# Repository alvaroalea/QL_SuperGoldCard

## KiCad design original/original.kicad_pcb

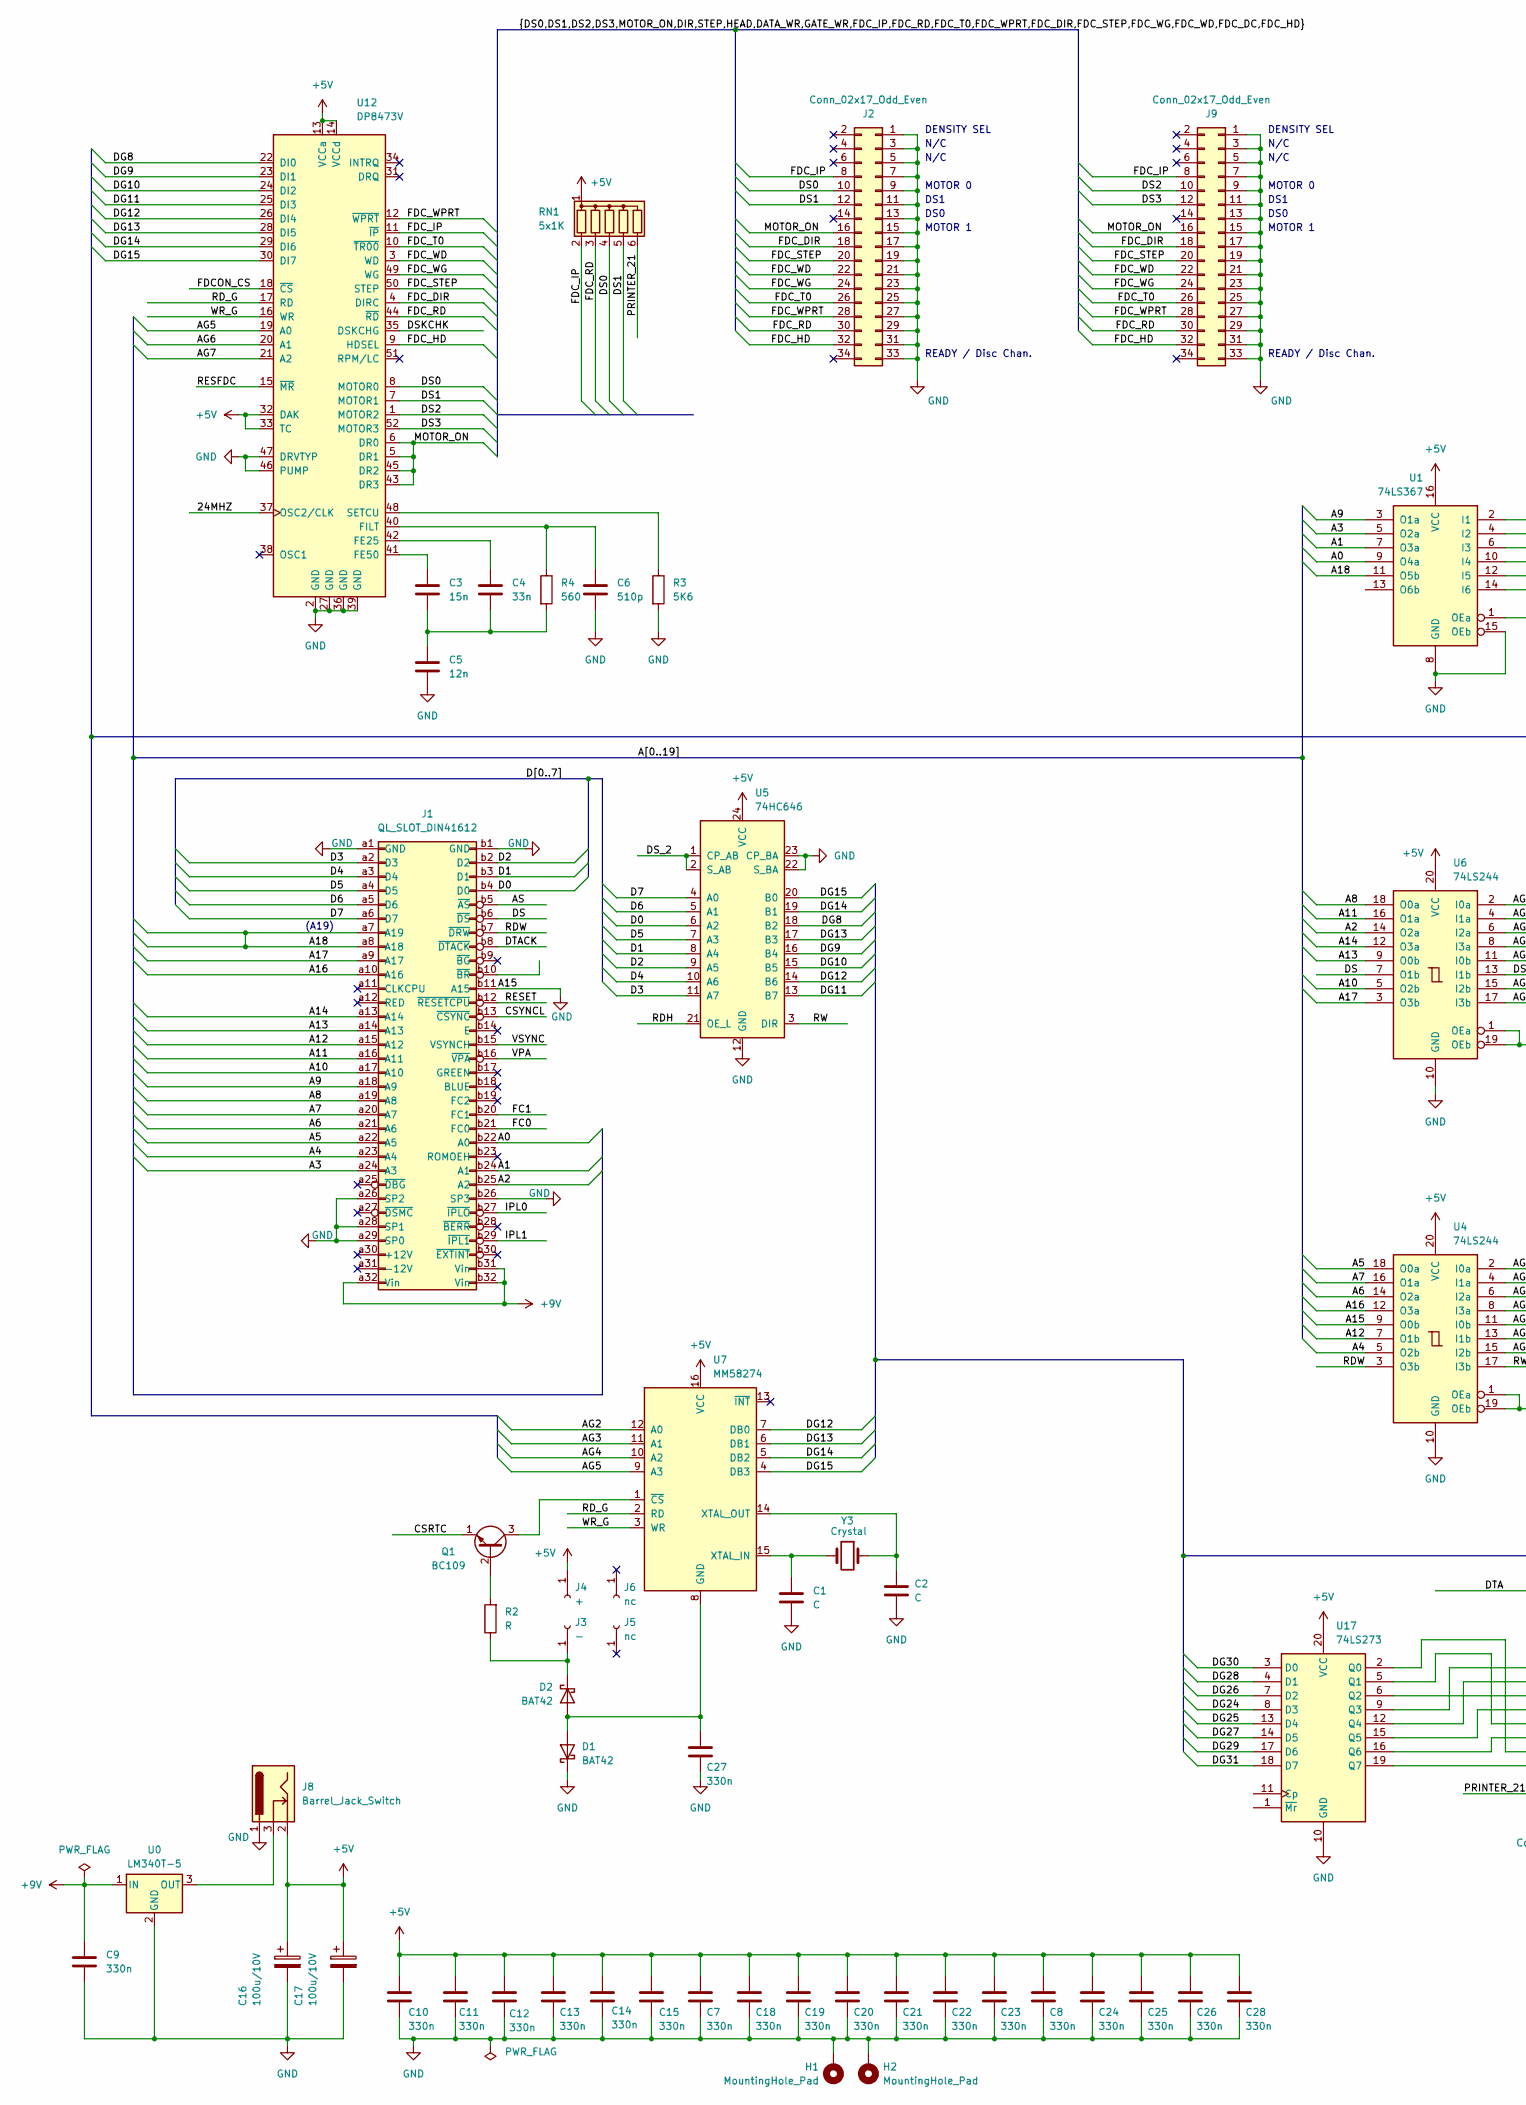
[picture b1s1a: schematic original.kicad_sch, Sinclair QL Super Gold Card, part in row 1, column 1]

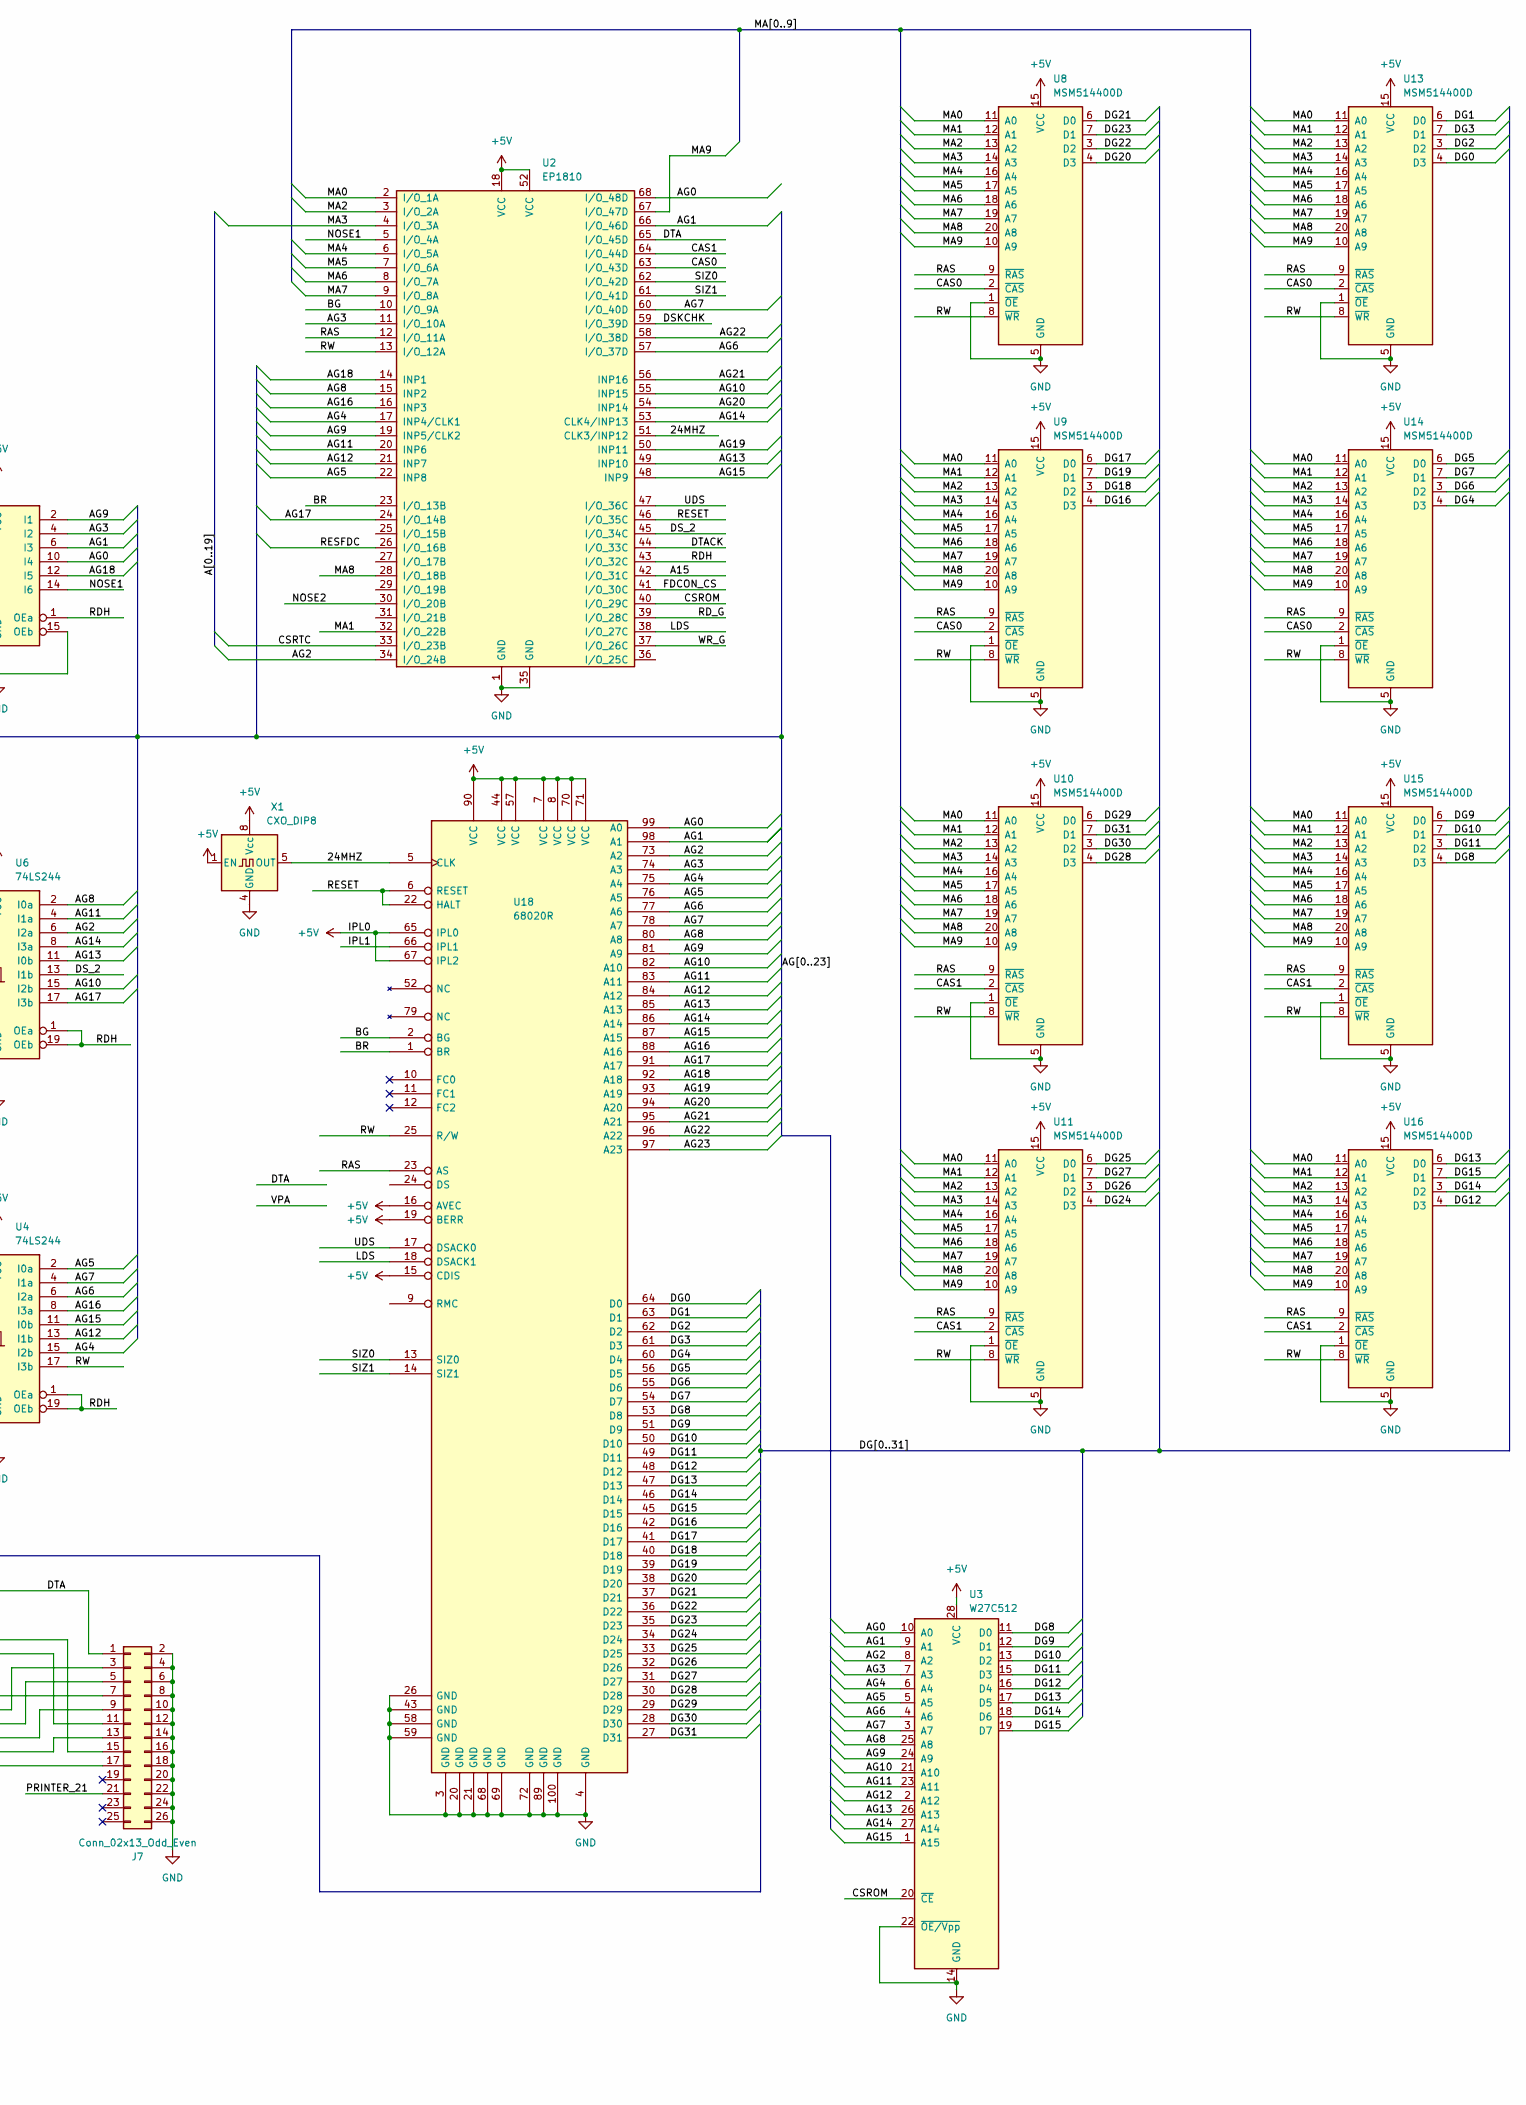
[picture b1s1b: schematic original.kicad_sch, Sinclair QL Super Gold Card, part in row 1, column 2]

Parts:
C1, C2: C; C_Disc_D3.0mm_W1.6mm_P2.50mm
C3: 15n; C_Rect_L16.5mm_W4.7mm_P15.00mm_MKT
C4: 33n; C_Rect_L16.5mm_W4.7mm_P15.00mm_MKT
C5: 12n; C_Rect_L11.5mm_W4.0mm_P10.00mm_MKT
C6: 510p; C_Rect_L11.0mm_W2.8mm_P10.00mm_MKT
C7, C8, C9, C10, C12, C13, C14, C15, C18, C19, C20, C21, C22, C23, C24, C25, C26, C27, C28: 330n; C_Disc_D3.0mm_W1.6mm_P2.50mm
C11: 330n; C_Disc_D3.8mm_W2.6mm_P2.50mm
C16, C17: 100u/10V; CP_Radial_D6.3mm_P2.50mm
D1, D2: BAT42; D_DO-35_SOD27_P7.62mm_Horizontal
H1, H2: MountingHole_Pad; MountingHole_2.5mm_Pad_Via
J1: QL_SLOT_DIN41612; DIN41612_B_2x32_Female_Horizontal_THT
J2: Conn_02x17_Odd_Even; PinHeader_2x17_P2.54mm_Horizontal
J3: -; PinSocket_1x01_P2.54mm_Vertical
J4: +; PinSocket_1x01_P2.54mm_Vertical
J5, J6: nc; PinSocket_1x01_P2.54mm_Vertical
J7: Conn_02x13_Odd_Even; PinHeader_2x13_P2.54mm_Horizontal
J8: Barrel_Jack_Switch; BarrelJack_CUI_PJ-102AH_Horizontal
J9: Conn_02x17_Odd_Even; PinHeader_2x17_P2.54mm_Vertical
Q1: BC109; TO-18-3
R2: R; R_Axial_DIN0204_L3.6mm_D1.6mm_P7.62mm_Horizontal
R3: 5K6; R_Axial_DIN0204_L3.6mm_D1.6mm_P7.62mm_Horizontal
R4: 560; R_Axial_DIN0204_L3.6mm_D1.6mm_P7.62mm_Horizontal
RN1: 5x1K; R_Array_SIP6
U0: LM340T-5; TO-220-3_Vertical
U1: 74LS367; DIP-16_W7.62mm
U2: EP1810; PLCC-68_THT-Socket
U3: W27C512; DIP-28_W15.24mm
U4, U6: 74LS244; DIP-20_W7.62mm
U5: 74HC646; DIP-24_W7.62mm
U7: MM58274; DIP-16_W7.62mm
U8, U9, U10, U11, U13, U14, U15, U16: MSM514400D; ZIP-20_W5.08mm
U12: DP8473V; PLCC-52_THT-Socket
U17: 74LS273; DIP-20_W7.62mm
U18: 68020R; PQFP-100_14x20mm_P0.65mm
X1: CXO_DIP8; Oscillator_SeikoEpson_SG-8002DC
Y3: Crystal; Crystal_AT310_D3.0mm_L10.0mm_Vertical

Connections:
+5V: C7.1, C8.1, C10.1, C11.1, C12.1, C13.1, C14.1, C15.1, C16.1, C17.1, C18.1, C19.1, C20.1, C21.1, C22.1, C23.1, C24.1, C25.1, C26.1, C28.1, J1.b27 (~IPLO), J4.1, J8.2, RN1.1 (common), U1.16 (VCC), U2.18 (VCC), U2.52 (VCC), U3.28 (VCC), U4.20 (VCC), U5.24 (VCC), U6.20 (VCC), U7.16 (VCC), U8.15 (VCC), U9.15 (VCC), U10.15 (VCC), U11.15 (VCC), U12.13 (VCCa), U12.14 (VCCd), U12.32 (DAK), U12.33 (TC), U13.15 (VCC), U14.15 (VCC), U15.15 (VCC), U16.15 (VCC), U17.20 (VCC), U18.7 (VCC), U18.8 (VCC), U18.15 (CDIS), U18.16 (AVEC), U18.19 (BERR), U18.44 (VCC), U18.57 (VCC), U18.65 (IPL0), U18.67 (IPL2), U18.70 (VCC), U18.71 (VCC), U18.90 (VCC), X1.1 (EN), X1.8 (Vcc)
+9V: C9.1, J1.a32 (Vin), J1.b31 (Vin), J1.b32 (Vin), U0.1 (IN)
/24MHZ: U2.51 (CLK3/INP12), U12.37 (OSC2/CLK), U18.5 (CLK), X1.5 (OUT)
/A0: J1.b22 (A0), U1.9 (O4a)
/A1: J1.b24 (A1), U1.7 (O3a)
/A2: J1.b25 (A2), U6.14 (O2a)
/A3: J1.a24 (A3), U1.5 (O2a)
/A4: J1.a23 (A4), U4.5 (O2b)
/A5: J1.a22 (A5), U4.18 (O0a)
/A6: J1.a21 (A6), U4.14 (O2a)
/A7: J1.a20 (A7), U4.16 (O1a)
/A8: J1.a19 (A8), U6.18 (O0a)
/A9: J1.a18 (A9), U1.3 (O1a)
/A10: J1.a17 (A10), U6.5 (O2b)
/A11: J1.a16 (A11), U6.16 (O1a)
/A12: J1.a15 (A12), U4.7 (O1b)
/A13: J1.a14 (A13), U6.9 (O0b)
/A14: J1.a13 (A14), U6.12 (O3a)
/A16: J1.a10 (A16), U4.12 (O3a)
/A17: J1.a9 (A17), U6.3 (O3b)
/A18: J1.a7 (A19), J1.a8 (A18), U1.11 (O5b)
/AG0: U1.10 (I4), U2.68 (I/O_48D), U3.10 (A0), U18.99 (A0)
/AG1: U1.6 (I3), U2.66 (I/O_46D), U3.9 (A1), U18.98 (A1)
/AG2: U2.34 (I/O_24B), U3.8 (A2), U6.6 (I2a), U7.12 (A0), U18.73 (A2)
/AG3: U1.4 (I2), U2.11 (I/O_10A), U3.7 (A3), U7.11 (A1), U18.74 (A3)
/AG4: U2.17 (INP4/CLK1), U3.6 (A4), U4.15 (I2b), U7.10 (A2), U18.75 (A4)
/AG5: U2.22 (INP8), U3.5 (A5), U4.2 (I0a), U7.9 (A3), U12.19 (A0), U18.76 (A5)
/AG6: U2.57 (I/O_37D), U3.4 (A6), U4.6 (I2a), U12.20 (A1), U18.77 (A6)
/AG7: U2.60 (I/O_40D), U3.3 (A7), U4.4 (I1a), U12.21 (A2), U18.78 (A7)
/AG8: U2.15 (INP2), U3.25 (A8), U6.2 (I0a), U18.80 (A8)
/AG9: U1.2 (I1), U2.19 (INP5/CLK2), U3.24 (A9), U18.81 (A9)
/AG10: U2.55 (INP15), U3.21 (A10), U6.15 (I2b), U18.82 (A10)
/AG11: U2.20 (INP6), U3.23 (A11), U6.4 (I1a), U18.83 (A11)
/AG12: U2.21 (INP7), U3.2 (A12), U4.13 (I1b), U18.84 (A12)
/AG13: U2.49 (INP10), U3.26 (A13), U6.11 (I0b), U18.85 (A13)
/AG14: U2.53 (CLK4/INP13), U3.27 (A14), U6.8 (I3a), U18.86 (A14)
/AG15: U2.48 (INP9), U3.1 (A15), U4.11 (I0b), U18.87 (A15)
/AG16: U2.16 (INP3), U4.8 (I3a), U18.88 (A16)
/AG17: U2.24 (I/O_14B), U6.17 (I3b), U18.91 (A17)
/AG18: U1.12 (I5), U2.14 (INP1), U18.92 (A18)
/AG19: U2.50 (INP11), U18.93 (A19)
/AG20: U2.54 (INP14), U18.94 (A20)
/AG21: U2.56 (INP16), U18.95 (A21)
/AG22: U2.58 (I/O_38D), U18.96 (A22)
/AG23: U18.97 (A23)
/AS: J1.b5 (~AS)
/BG: U2.10 (I/O_9A), U18.2 (BG)
/BR: U2.23 (I/O_13B), U18.1 (BR)
/CAS0: U2.63 (I/O_43D), U8.2 (~CAS), U9.2 (~CAS), U13.2 (~CAS), U14.2 (~CAS)
/CAS1: U2.64 (I/O_44D), U10.2 (~CAS), U11.2 (~CAS), U15.2 (~CAS), U16.2 (~CAS)
/CSROM: U2.40 (I/O_29C), U3.20 (~CE)
/CSRTC: Q1.1 (E), U2.33 (I/O_23B)
/CSYNCL: J1.b13 (~CSYNC)
/D0: J1.b4 (D0), U5.6 (A2)
/D1: J1.b3 (D1), U5.8 (A4)
/D2: J1.b2 (D2), U5.9 (A5)
/D3: J1.a2 (D3), U5.11 (A7)
/D4: J1.a3 (D4), U5.10 (A6)
/D5: J1.a4 (D5), U5.7 (A3)
/D6: J1.a5 (D6), U5.5 (A1)
/D7: J1.a6 (D7), U5.4 (A0)
/DG0: U13.4 (D3), U18.64 (D0)
/DG1: U13.6 (D0), U18.63 (D1)
/DG2: U13.3 (D2), U18.62 (D2)
/DG3: U13.7 (D1), U18.61 (D3)
/DG4: U14.4 (D3), U18.60 (D4)
/DG5: U14.6 (D0), U18.56 (D5)
/DG6: U14.3 (D2), U18.55 (D6)
/DG7: U14.7 (D1), U18.54 (D7)
/DG8: U3.11 (D0), U5.18 (B2), U12.22 (DI0), U15.4 (D3), U18.53 (D8)
/DG9: U3.12 (D1), U5.16 (B4), U12.23 (DI1), U15.6 (D0), U18.51 (D9)
/DG10: U3.13 (D2), U5.15 (B5), U12.24 (DI2), U15.7 (D1), U18.50 (D10)
/DG11: U3.15 (D3), U5.13 (B7), U12.25 (DI3), U15.3 (D2), U18.49 (D11)
/DG12: U3.16 (D4), U5.14 (B6), U7.7 (DB0), U12.26 (DI4), U16.4 (D3), U18.48 (D12)
/DG13: U3.17 (D5), U5.17 (B3), U7.6 (DB1), U12.28 (DI5), U16.6 (D0), U18.47 (D13)
/DG14: U3.18 (D6), U5.19 (B1), U7.5 (DB2), U12.29 (DI6), U16.3 (D2), U18.46 (D14)
/DG15: U3.19 (D7), U5.20 (B0), U7.4 (DB3), U12.30 (DI7), U16.7 (D1), U18.45 (D15)
/DG16: U9.4 (D3), U18.42 (D16)
/DG17: U9.6 (D0), U18.41 (D17)
/DG18: U9.3 (D2), U18.40 (D18)
/DG19: U9.7 (D1), U18.39 (D19)
/DG20: U8.4 (D3), U18.38 (D20)
/DG21: U8.6 (D0), U18.37 (D21)
/DG22: U8.3 (D2), U18.36 (D22)
/DG23: U8.7 (D1), U18.35 (D23)
/DG24: U11.4 (D3), U17.8 (D3), U18.34 (D24)
/DG25: U11.6 (D0), U17.13 (D4), U18.33 (D25)
/DG26: U11.3 (D2), U17.7 (D2), U18.32 (D26)
/DG27: U11.7 (D1), U17.14 (D5), U18.31 (D27)
/DG28: U10.4 (D3), U17.4 (D1), U18.30 (D28)
/DG29: U10.6 (D0), U17.17 (D6), U18.29 (D29)
/DG30: U10.3 (D2), U17.3 (D0), U18.28 (D30)
/DG31: U10.7 (D1), U17.18 (D7), U18.27 (D31)
/DS: J1.b6 (~DS), U6.7 (O1b)
/DS0: J2.10, RN1.4 (R3), U12.8 (MOTOR0)
/DS1: J2.12, RN1.5 (R4), U12.7 (MOTOR1)
/DS2: J9.10, U12.1 (MOTOR2)
/DS3: J9.12, U12.52 (MOTOR3)
/DSKCHK: U2.59 (I/O_39D), U12.35 (DSKCHG)
/DS_2: U2.45 (I/O_34C), U5.1 (CP_AB), U5.2 (S_AB), U6.13 (I1b)
/DTA: J7.1, U2.65 (I/O_45D)
/DTACK: J1.b8 (~DTACK), U2.44 (I/O_33C)
/FC0: J1.b21 (FC0)
/FC1: J1.b20 (FC1)
/FDCON_CS: U2.41 (I/O_30C), U12.18 (~CS)
/FDC_DIR: J2.18, J9.18, U12.4 (DIRC)
/FDC_HD: J2.32, J9.32, U12.9 (HDSEL)
/FDC_IP: J2.8, J9.8, RN1.2 (R1), U12.11 (~IP)
/FDC_RD: J2.30, J9.30, RN1.3 (R2), U12.44 (~RD)
/FDC_STEP: J2.20, J9.20, U12.50 (STEP)
/FDC_T0: J2.26, J9.26, U12.10 (~TR00)
/FDC_WD: J2.22, J9.22, U12.3 (WD)
/FDC_WG: J2.24, J9.24, U12.49 (WG)
/FDC_WPRT: J2.28, J9.28, U12.12 (~WPRT)
/IPL1: J1.b29 (~IPL1), U18.66 (IPL1)
/LDS: U2.38 (I/O_27C), U18.18 (DSACK1)
/MA0: U2.2 (I/O_1A), U8.11 (A0), U9.11 (A0), U10.11 (A0), U11.11 (A0), U13.11 (A0), U14.11 (A0), U15.11 (A0), U16.11 (A0)
/MA1: U2.32 (I/O_22B), U8.12 (A1), U9.12 (A1), U10.12 (A1), U11.12 (A1), U13.12 (A1), U14.12 (A1), U15.12 (A1), U16.12 (A1)
/MA2: U2.3 (I/O_2A), U8.13 (A2), U9.13 (A2), U10.13 (A2), U11.13 (A2), U13.13 (A2), U14.13 (A2), U15.13 (A2), U16.13 (A2)
/MA3: U2.4 (I/O_3A), U8.14 (A3), U9.14 (A3), U10.14 (A3), U11.14 (A3), U13.14 (A3), U14.14 (A3), U15.14 (A3), U16.14 (A3)
/MA4: U2.6 (I/O_5A), U8.16 (A4), U9.16 (A4), U10.16 (A4), U11.16 (A4), U13.16 (A4), U14.16 (A4), U15.16 (A4), U16.16 (A4)
/MA5: U2.7 (I/O_6A), U8.17 (A5), U9.17 (A5), U10.17 (A5), U11.17 (A5), U13.17 (A5), U14.17 (A5), U15.17 (A5), U16.17 (A5)
/MA6: U2.8 (I/O_7A), U8.18 (A6), U9.18 (A6), U10.18 (A6), U11.18 (A6), U13.18 (A6), U14.18 (A6), U15.18 (A6), U16.18 (A6)
/MA7: U2.9 (I/O_8A), U8.19 (A7), U9.19 (A7), U10.19 (A7), U11.19 (A7), U13.19 (A7), U14.19 (A7), U15.19 (A7), U16.19 (A7)
/MA8: U2.28 (I/O_18B), U8.20 (A8), U9.20 (A8), U10.20 (A8), U11.20 (A8), U13.20 (A8), U14.20 (A8), U15.20 (A8), U16.20 (A8)
/MA9: U2.67 (I/O_47D), U8.10 (A9), U9.10 (A9), U10.10 (A9), U11.10 (A9), U13.10 (A9), U14.10 (A9), U15.10 (A9), U16.10 (A9)
/MOTOR_ON: J2.16, J9.16, U12.5 (DR1), U12.6 (DR0), U12.43 (DR3), U12.45 (DR2)
/NOSE1: U1.14 (I6), U2.5 (I/O_4A)
/NOSE2: U2.30 (I/O_20B)
/PRINTER_21: J7.21, RN1.6 (R5)
/RAS: U2.12 (I/O_11A), U8.9 (~RAS), U9.9 (~RAS), U10.9 (~RAS), U11.9 (~RAS), U13.9 (~RAS), U14.9 (~RAS), U15.9 (~RAS), U16.9 (~RAS), U18.23 (AS)
/RDH: U1.1 (OEa), U2.43 (I/O_32C), U4.1 (OEa), U4.19 (OEb), U5.21 (OE_L), U6.1 (OEa), U6.19 (OEb)
/RDW: J1.b7 (~DRW), U4.3 (O3b)
/RD_G: U2.39 (I/O_28C), U7.2 (RD), U12.17 (RD)
/RESET: J1.b12 (~RESETCPU), U2.46 (I/O_35C), U18.6 (RESET), U18.22 (HALT)
/RESFDC: U2.26 (I/O_16B), U12.15 (~MR)
/RW: U2.13 (I/O_12A), U4.17 (I3b), U5.3 (DIR), U8.8 (~WR), U9.8 (~WR), U10.8 (~WR), U11.8 (~WR), U13.8 (~WR), U14.8 (~WR), U15.8 (~WR), U16.8 (~WR), U18.25 (R/W)
/SIZ0: U2.62 (I/O_42D), U18.13 (SIZ0)
/SIZ1: U2.61 (I/O_41D), U18.14 (SIZ1)
/UDS: U2.47 (I/O_36C), U18.17 (DSACK0)
/VPA: J1.b16 (~VPA)
/VSYNC: J1.b15 (VSYNCH)
/WR_G: U2.37 (I/O_26C), U7.3 (WR), U12.16 (WR)
GND: C1.2, C2.2, C5.2, C6.2, C7.2, C8.2, C9.2, C10.2, C11.2, C12.2, C13.2, C14.2, C15.2, C16.2, C17.2, C18.2, C19.2, C20.2, C21.2, C22.2, C23.2, C24.2, C25.2, C26.2, C27.2, C28.2, D1.1 (K), H1.1, H2.1, J1.a1 (GND), J1.a26 (SP2), J1.a28 (SP1), J1.a29 (SP0), J1.b1 (GND), J1.b11 (A15), J1.b26 (SP3), J2.1, J2.3, J2.5, J2.7, J2.9, J2.11, J2.13, J2.15, J2.17, J2.19, J2.21, J2.23, J2.25, J2.27, J2.29, J2.31, J2.33, J7.2, J7.4, J7.6, J7.8, J7.10, J7.12, J7.14, J7.16, J7.18, J7.20, J7.22, J7.24, J7.26, J8.1, J9.1, J9.3, J9.5, J9.7, J9.9, J9.11, J9.13, J9.15, J9.17, J9.19, J9.21, J9.23, J9.25, J9.27, J9.29, J9.31, J9.33, R3.2, U0.2 (GND), U1.8 (GND), U1.15 (OEb), U2.1 (GND), U2.35 (GND), U2.42 (I/O_31C), U3.14 (GND), U3.22 (~OE/Vpp), U4.9 (O0b), U4.10 (GND), U5.12 (GND), U5.22 (S_BA), U5.23 (CP_BA), U6.10 (GND), U8.1 (~OE), U8.5 (GND), U9.1 (~OE), U9.5 (GND), U10.1 (~OE), U10.5 (GND), U11.1 (~OE), U11.5 (GND), U12.2 (GND), U12.27 (GND), U12.36 (GND), U12.39 (GND), U12.46 (PUMP), U12.47 (DRVTYP), U13.1 (~OE), U13.5 (GND), U14.1 (~OE), U14.5 (GND), U15.1 (~OE), U15.5 (GND), U16.1 (~OE), U16.5 (GND), U17.10 (GND), U18.3 (GND), U18.4 (GND), U18.20 (GND), U18.21 (GND), U18.26 (GND), U18.43 (GND), U18.58 (GND), U18.59 (GND), U18.68 (GND), U18.69 (GND), U18.72 (GND), U18.89 (GND), U18.100 (GND), X1.4 (GND)
unnamed: C3.2, C4.2, C5.1, R4.2
unnamed: C27.1, D1.2 (A), D2.2 (A), U7.8 (GND)
unnamed: D2.1 (K), J3.1, R2.1
unnamed: J7.3, U17.9 (Q3)
unnamed: J7.5, U17.12 (Q4)
unnamed: J7.7, U17.6 (Q2)
unnamed: J7.9, U17.15 (Q5)
unnamed: J7.11, U17.5 (Q1)
unnamed: J7.13, U17.16 (Q6)
unnamed: J7.15, U17.2 (Q0)
unnamed: J7.17, U17.19 (Q7)
unnamed: Q1.2 (B), R2.2
unnamed: Q1.3 (C), U7.1 (~CS)
unnamed: J8.3, U0.3 (OUT)
unnamed: C1.1, U7.15 (XTAL_IN), Y3.2
unnamed: C2.1, U7.14 (XTAL_OUT), Y3.1
unnamed: C4.1, U12.42 (FE25)
unnamed: C3.1, U12.41 (FE50)
unnamed: C6.1, R4.1, U12.40 (FILT)
unnamed: R3.1, U12.48 (SETCU)

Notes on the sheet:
N/C
DENSITY SEL
DS1
MOTOR 0
DS0
MOTOR 1
READY / Disc Chan.
(A19)

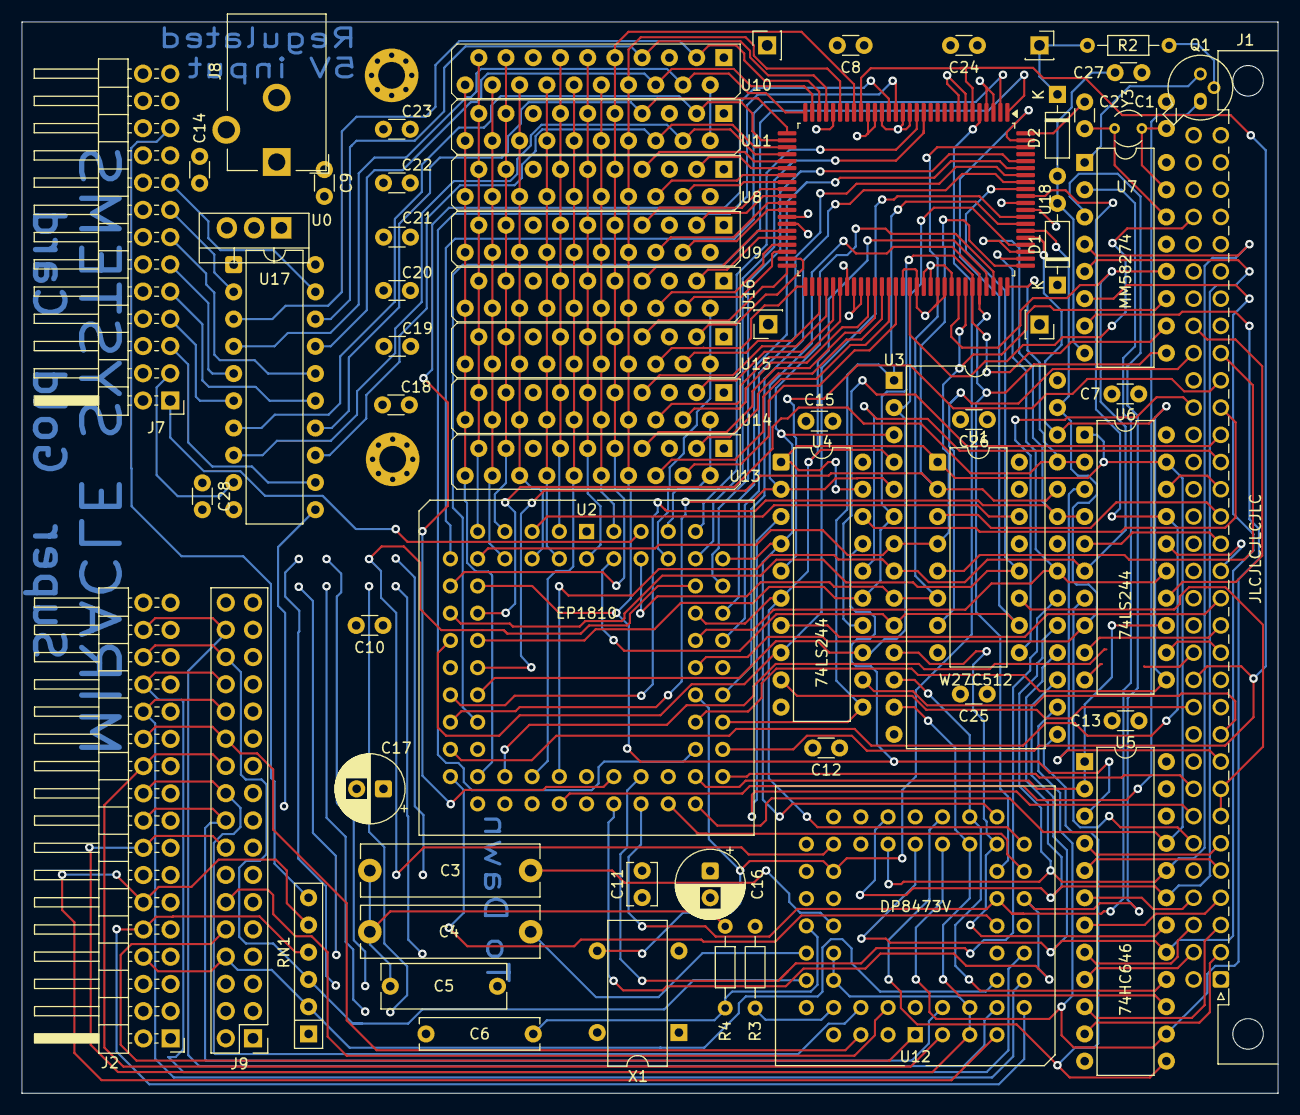
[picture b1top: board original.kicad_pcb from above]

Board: 4 copper layers, 117.2 x 99.9 mm, 67 parts (0 on the bottom side), 156 nets.

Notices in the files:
original/original.kicad_pcb:
Licensed under Cern OHL-S - https://ohwr.org/cern_ohl_s_v2.txt
